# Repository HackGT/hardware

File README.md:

# HackGT Hardware
Custom PCBs, electronics, and embedded hardware solutions

PCBs are designed with EAGLE.

Code can be built and flashed with the Arduino IDE with [ATtiny Core](https://github.com/SpenceKonde/ATTinyCore) installed.
* Be sure to configure the right board, clock speed, etc. in the Tools menu
* With new chips or when changing chip settings, select "Burn Bootloader" to set the correct fuses on the microcontroller (or else uploading code won't work)
	* All of the PCBs listed here do not use a bootloader and must have code uploaded over an ISP programmer
* Upload with Sketch -> Upload Using Programmer (*not* regular Upload -- that's only for Arduinos with a bootloader connected over Serial)
	* To flash manually (saves time when flashing many boards because compilation only happens once), Sketch -> Export compiled Binary. This will export a .hex file that you can then upload with `"C:\Program Files (x86)\Arduino\hardware\tools\avr\bin\avrdude.exe" -c usbasp -p t167 -U flash:w:sketch_name.hex` where `usbasp` is your ISP programmer type and `t167` is the microcontroller specifier.

## Insight

* PCB: `PCBs/checkin-tiny/tiny.brd`
* Code: `Code/Insight` and `Code/Insight_Base` (for Arduino MEGA base station)
* Microcontroller: ATtiny167 @ 8 MHz internal clock
* VCC voltage: 3.3V (**Note: this device *requires* a 5V to 3.3V ISP level shifter to be programmed**)
* Features: 915 MHz radio, MFRC522 NFC interface, USB-C rechargeable battery, 20 pin expansion port

Insight is an inexpensive, handheld board designed to be distributed to sponsors at HackGT's events. It contains an NFC reader on one end and a 915 MHz radio on the other. In typical usage, sponsors scan participant badges over NFC, the device relays the decoded participant UUID to the base station (see below), which pops the participant's information (e.g. name, resume, favorite programming languages) up on the sponsor's phone or laptop. See [HackGT Insight](https://github.com/HackGT/insight) for more information. A 915 MHz radio is used instead of Wi-Fi due to reduced cost, reduced microcontroller requirements, and so that it will have available usable bandwidth even with thousands of 2.4 GHz radios (Wi-Fi / Bluetooth) active during a HackGT event.

The base station consists of an Arduino MEGA with an Ethernet Shield and an [Adafruit RFM69HCW radio module](https://www.adafruit.com/product/3070) added.

### Tech details:
* Power is *always* supplied from the 18650 Lithium Ion battery. This means that a battery must be installed for the device to work -- even if the USB-C connection is plugged in.
* The device **does not have reverse polarity protection**. Always double check the orientation of the Li-Ion battery.
* Voltage is stepped down from the battery's 4.2 volts (max) to 3.5 volts (min) to 3.3 volts VCC by a [linear low-dropout regulator](http://www.ti.com/lit/ds/symlink/tps736.pdf). This regulator drops out at 3.5 volts and can supply up to 400 mA of current.
* USB charging occurs at up to 500 mA (limit of charging IC chosen).
* MFRC522 (NFC) and RFM69HCW (radio) are connected to the ATtiny167 over the chip's hardware SPI bus. The SPI chip select lines are pulled high to deselect them when the ATtiny is programmed over ISP.
* A voltage divider with 4.7K ohm and 10K ohm resistors is used to measure the current battery level from the ATtiny's ADC. This read 10-bit value can then be easily converted to a voltage and/or battery percentage. See `Insight` and `Insight_Base` for the code that does this.
* A TTL serial header is exposed on the bottom edge of the PCB for debugging use. This header does not need to be soldered for final production devices.

### 20-pin expansion header
This device supports shields / daughterboard expansions using the 20-pin expansion header.

With board oriented as seen above:
```
[ 2 | 4 | 6 | 8 | 10 | 12 | 14 | 16 | 18 | 20 ]
[ 1 | 3 | 5 | 7 | 9  | 11 | 13 | 15 | 17 | 19 ]
```

Pin | Signal
----|-------
1 | V_USB (5 volts when USB plugged in, can also be used to charge battery)
2 | V3.3 (3.3 volts when switched on)
3 | RF_IRQ (radio to microcontroller interrupt)
4 | GND
5 | RX (TTL receive)
6 | RED (red status LED)
7 | TX (TTL transmit)
8 | GREEN (green status LED)
9 | BAT_REF (raw voltage divided battery reference, 3.3V safe)
10 | SPEAKER (connected to piezo buzzer, use with `tone()`)
11 | AUX0 (reserved for future use)
12 | NFC_RST (MRFC522 reset)
13 | CE0 (radio SPI chip select)
14 | CE1 (NFC SPI chip select)
15 | MISO (SPI / ISP)
16 | V_USB
17 | SCK (SPI / ISP)
18 | MOSI (SPI/ ISP)
19 | RST (ATtiny reset, ISP)
20 | GND

## ISP 5V to 3.3V Level Shifter

* PCB: `PCBs/checkin-tiny/shifter.brd`
* Code: N/A
* Primary IC: ‎SN74LVC245AN logic level shifter
* VCC voltage: 5V input, 3.3V output

Nearly all HackGT hardware must be programmed over ISP, a protocol used by AVR microcontrollers based on the SPI standard. This can be done with $6 USB programmers such as [this one](https://www.amazon.com/HiLetgo-ATMEGA8-Programmer-USBasp-Cable/dp/B00AX4WQ00). However, note that even though this programmer claims to support 3.3V operation, this only applies to the VCC pin; the signal lines will still operate at 5V. This can damage 5V intolerant devices connected to the SPI bus (e.g. the MFRC522 NFC chip and RFM69HCW radio on Insight).

This tiny board connects to the 6-pin ISP header on the top, shifts the VCC and signal lines down to 3.3 volts, and then outputs these signals on the output ISP header on the bottom. Note that the USB programmer must be outputting 5 volts for this shifter to work correctly so be sure to configure it for 5 volt *not* 3.3 volt output.

**Be sure to double check the correct ISP header orientation when soldering the male/female headers on!**

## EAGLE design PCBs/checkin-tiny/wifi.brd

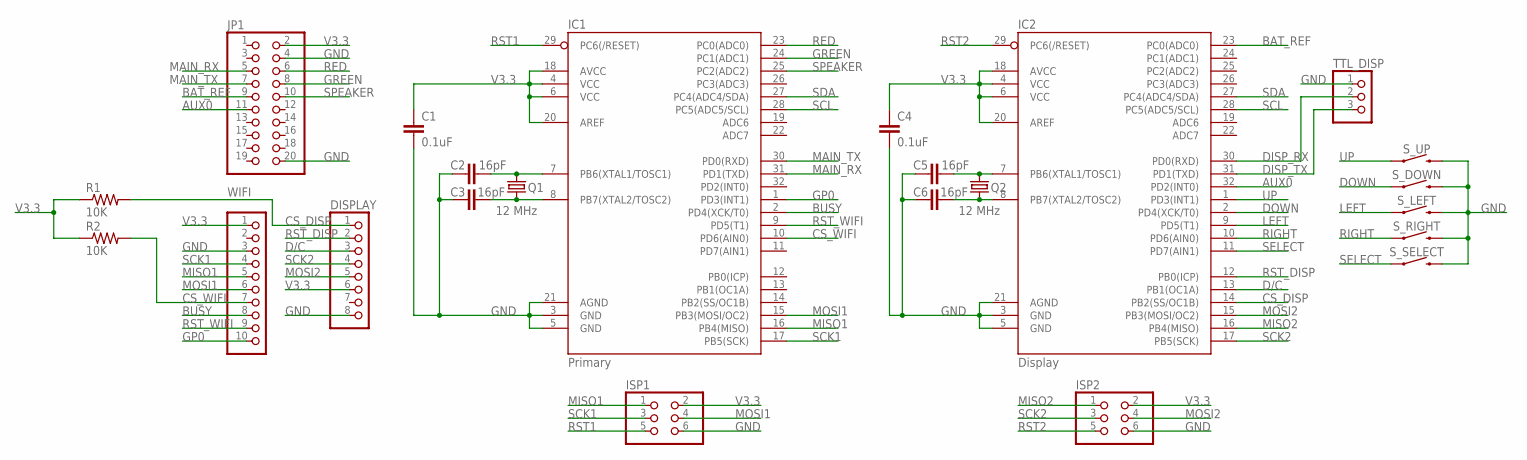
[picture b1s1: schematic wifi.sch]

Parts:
C1, C4: 0.1uF; C1206
C2, C3, C5, C6: 16pF; C1206
DISPLAY: PINHD-1X8CLEANBIG; 1X08-CLEANBIG
IC1: Primary; TQFP32-08
IC2: Display; TQFP32-08
ISP1, ISP2: PINHD-2X3; 2X03
JP1: PINHD-2X10; 2X10
Q1, Q2: 12 MHz; HC49/S
R1, R2: 10K; R1206
S_DOWN: MOMENTARY-SWITCH-SPST-PTH-6.0MM; TACTILE_SWITCH_PTH_6.0MM
S_LEFT: MOMENTARY-SWITCH-SPST-PTH-6.0MM; TACTILE_SWITCH_PTH_6.0MM
S_RIGHT: MOMENTARY-SWITCH-SPST-PTH-6.0MM; TACTILE_SWITCH_PTH_6.0MM
S_SELECT: MOMENTARY-SWITCH-SPST-PTH-6.0MM; TACTILE_SWITCH_PTH_6.0MM
S_UP: MOMENTARY-SWITCH-SPST-PTH-6.0MM; TACTILE_SWITCH_PTH_6.0MM
TTL_DISP: PINHD-1X3; 1X03
WIFI: PINHD-1X10; 1X10-BIG

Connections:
AUX0: IC2.32 (PD2(INT0)), JP1.11
BAT_REF: IC2.23 (PC0(ADC0)), JP1.9
BUSY: IC1.2 (PD4(XCK/T0)), WIFI.8
CS_DISP: DISPLAY.1, IC2.14 (PB2(SS/OC1B)), R1.2
CS_WIFI: IC1.10 (PD6(AIN0)), R2.2, WIFI.7
D/C: DISPLAY.3, IC2.13 (PB1(OC1A))
DISP_RX: IC2.30 (PD0(RXD)), TTL_DISP.2
DISP_TX: IC2.31 (PD1(TXD)), TTL_DISP.3
DOWN: IC2.2 (PD4(XCK/T0)), S_DOWN.1
GND: C1.2, C2.1, C3.1, C4.2, C5.1, C6.1, DISPLAY.8, IC1.3 (GND), IC1.5 (GND), IC1.21 (AGND), IC2.3 (GND), IC2.5 (GND), IC2.21 (AGND), ISP1.6, ISP2.6, JP1.4, JP1.20, S_DOWN.3 (2), S_LEFT.3 (2), S_RIGHT.3 (2), S_SELECT.3 (2), S_UP.3 (2), TTL_DISP.1, WIFI.3
GP0: IC1.1 (PD3(INT1)), WIFI.10
GREEN: IC1.24 (PC1(ADC1)), JP1.8
LEFT: IC2.9 (PD5(T1)), S_LEFT.1
MAIN_RX: IC1.31 (PD1(TXD)), JP1.5
MAIN_TX: IC1.30 (PD0(RXD)), JP1.7
MISO1: IC1.16 (PB4(MISO)), ISP1.1, WIFI.5
MISO2: IC2.16 (PB4(MISO)), ISP2.1
MOSI1: IC1.15 (PB3(MOSI/OC2)), ISP1.4, WIFI.6
MOSI2: DISPLAY.5, IC2.15 (PB3(MOSI/OC2)), ISP2.4
unnamed: C5.2, IC2.7 (PB6(XTAL1/TOSC1)), Q2.2
unnamed: C6.2, IC2.8 (PB7(XTAL2/TOSC2)), Q2.1
unnamed: C2.2, IC1.7 (PB6(XTAL1/TOSC1)), Q1.2
unnamed: C3.2, IC1.8 (PB7(XTAL2/TOSC2)), Q1.1
RED: IC1.23 (PC0(ADC0)), JP1.6
RIGHT: IC2.10 (PD6(AIN0)), S_RIGHT.1
RST1: IC1.29 (PC6(/RESET)), ISP1.5
RST2: IC2.29 (PC6(/RESET)), ISP2.5
RST_DISP: DISPLAY.2, IC2.12 (PB0(ICP))
RST_WIFI: IC1.9 (PD5(T1)), WIFI.9
SCK1: IC1.17 (PB5(SCK)), ISP1.3, WIFI.4
SCK2: DISPLAY.4, IC2.17 (PB5(SCK)), ISP2.3
SCL: IC1.28 (PC5(ADC5/SCL)), IC2.28 (PC5(ADC5/SCL))
SDA: IC1.27 (PC4(ADC4/SDA)), IC2.27 (PC4(ADC4/SDA))
SELECT: IC2.11 (PD7(AIN1)), S_SELECT.1
SPEAKER: IC1.25 (PC2(ADC2)), JP1.10
UP: IC2.1 (PD3(INT1)), S_UP.1
V3.3: C1.1, C4.1, DISPLAY.6, IC1.4 (VCC), IC1.6 (VCC), IC1.18 (AVCC), IC1.20 (AREF), IC2.4 (VCC), IC2.6 (VCC), IC2.18 (AVCC), IC2.20 (AREF), ISP1.2, ISP2.2, JP1.2, R1.1, R2.1, WIFI.1

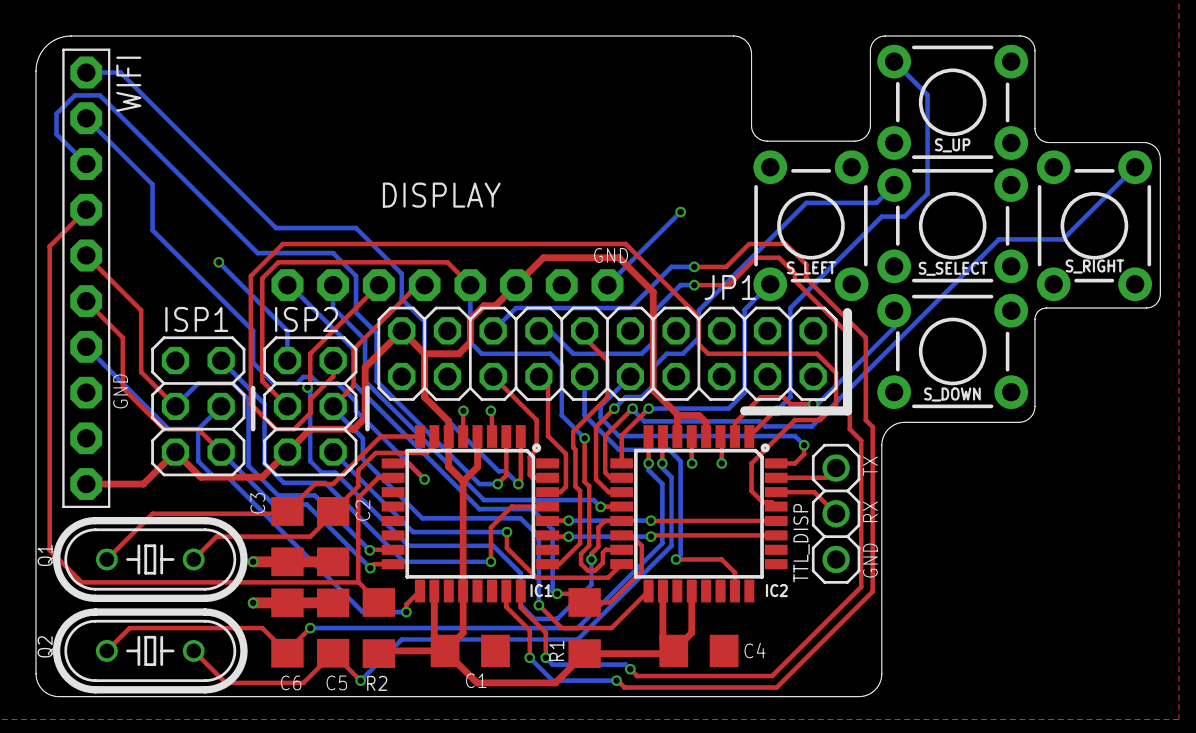
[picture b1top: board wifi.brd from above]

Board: 2 copper layers, 62.5 x 36.7 mm, 23 parts (0 on the bottom side), 37 nets.

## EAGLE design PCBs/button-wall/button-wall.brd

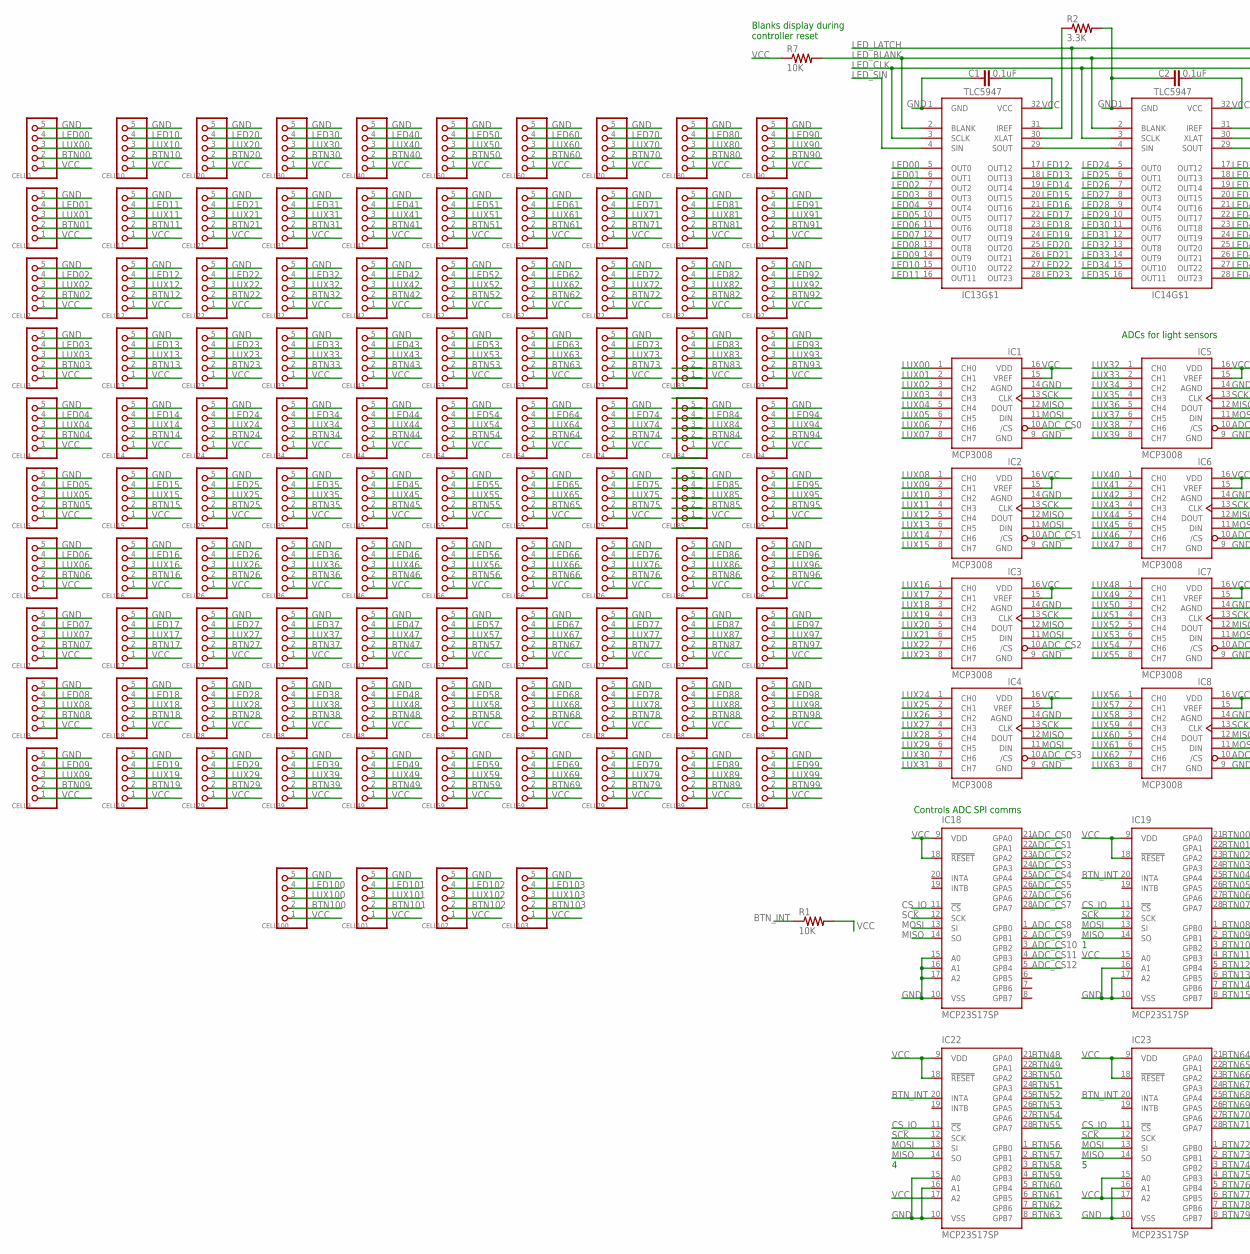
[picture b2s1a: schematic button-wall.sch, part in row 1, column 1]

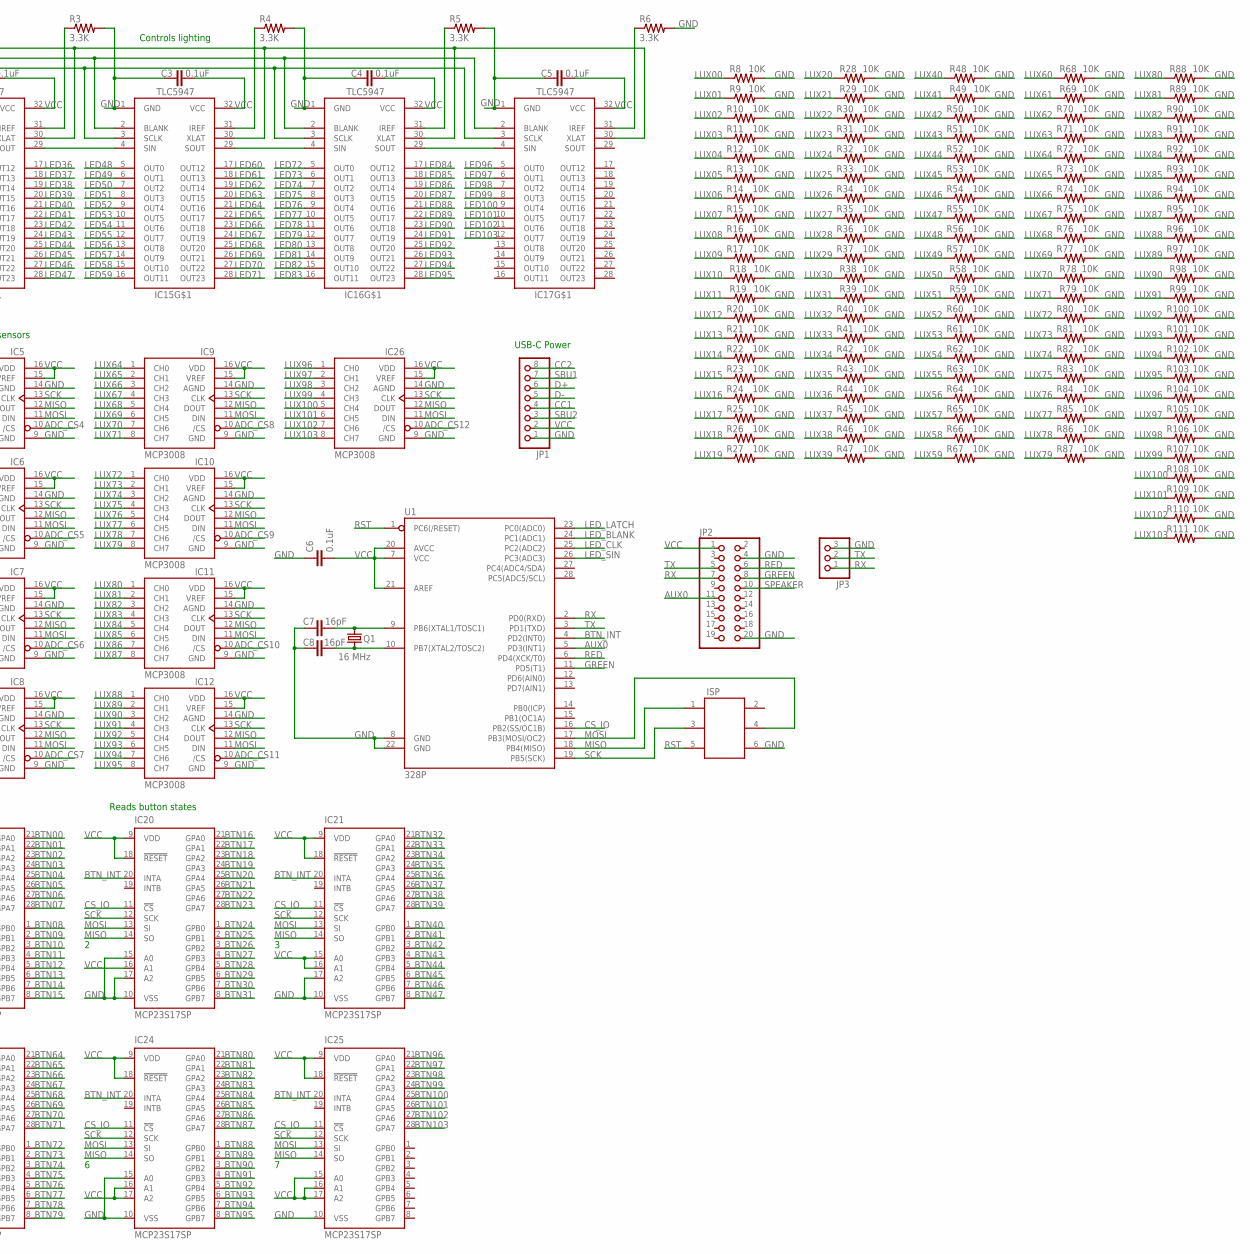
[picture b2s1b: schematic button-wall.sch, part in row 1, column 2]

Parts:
C1, C2, C3, C4, C5, C6: 0.1uF; C1206
C7, C8: 16pF; C0805
CELL0, CELL1, CELL2, CELL3, CELL4, CELL5, CELL6, CELL7, CELL8, CELL9, CELL10, CELL11, CELL12, CELL13, CELL14, CELL15, CELL16, CELL17, CELL18, CELL19, CELL20, CELL21, CELL22, CELL23, CELL24, CELL25, CELL26, CELL27, CELL28, CELL29, CELL30, CELL31, CELL32, CELL33, CELL34, CELL35, CELL36, CELL37, CELL38, CELL39, CELL40, CELL41, CELL42, CELL43, CELL44, CELL45, CELL46, CELL47, CELL48, CELL49, CELL50, CELL51, CELL52, CELL53, CELL54, CELL55, CELL56, CELL57, CELL58, CELL59, CELL60, CELL61, CELL62, CELL63, CELL64, CELL65, CELL66, CELL67, CELL68, CELL69, CELL70, CELL71, CELL72, CELL73, CELL74, CELL75, CELL76, CELL77, CELL78, CELL79, CELL80, CELL81, CELL82, CELL83, CELL84, CELL85, CELL86, CELL87, CELL88, CELL89, CELL90, CELL91, CELL92, CELL93, CELL94, CELL95, CELL96, CELL97, CELL98, CELL99, CELL100, CELL101, CELL102, CELL103: PINHD-1X55X2MM; 1_05X2MM
IC1, IC2, IC3, IC4, IC5, IC6, IC7, IC8, IC9, IC10, IC11, IC12, IC26: MCP3008; DIL16
IC13, IC14, IC15, IC16, IC17: TLC5947-DAP; HTSSOP32DAP
IC18, IC19, IC20, IC21, IC22, IC23, IC24, IC25: MCP23S17SP; DIL28-3
ISP: 61200621621
JP1: PINHD-1X8CLEANBIG; 1X08-CLEANBIG
JP2: PINHD-2X10; 2X10
JP3: PINHD-1X3; 1X03
Q1: 16 MHz; HC49/S
R1, R7: 10K; R1206
R2, R3, R4, R5, R6: 3.3K; R1206
R8, R9, R10, R11, R12, R13, R14, R15, R16, R17, R18, R19, R20, R21, R22, R23, R24, R25, R26, R27, R28, R29, R30, R31, R32, R33, R34, R35, R36, R37, R38, R39, R40, R41, R42, R43, R44, R45, R46, R47, R48, R49, R50, R51, R52, R53, R54, R55, R56, R57, R58, R59, R60, R61, R62, R63, R64, R65, R66, R67, R68, R69, R70, R71, R72, R73, R74, R75, R76, R77, R78, R79, R80, R81, R82, R83, R84, R85, R86, R87, R88, R89, R90, R91, R92, R93, R94, R95, R96, R97, R98, R99, R100, R101, R102, R103, R104, R105, R106, R107, R108, R109, R110, R111: 10K; R0805
U1: 328P; DIP28

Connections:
ADC_CS0: IC1.10 (/CS), IC18.21 (GPA0)
ADC_CS1: IC2.10 (/CS), IC18.22 (GPA1)
ADC_CS2: IC3.10 (/CS), IC18.23 (GPA2)
ADC_CS3: IC4.10 (/CS), IC18.24 (GPA3)
ADC_CS4: IC5.10 (/CS), IC18.25 (GPA4)
ADC_CS5: IC6.10 (/CS), IC18.26 (GPA5)
ADC_CS6: IC7.10 (/CS), IC18.27 (GPA6)
ADC_CS7: IC8.10 (/CS), IC18.28 (GPA7)
ADC_CS8: IC9.10 (/CS), IC18.1 (GPB0)
ADC_CS9: IC10.10 (/CS), IC18.2 (GPB1)
ADC_CS10: IC11.10 (/CS), IC18.3 (GPB2)
ADC_CS11: IC12.10 (/CS), IC18.4 (GPB3)
ADC_CS12: IC18.5 (GPB4), IC26.10 (/CS)
AUX0: JP2.11, U1.5 (PD3(INT1))
BTN00: CELL0.2, IC19.21 (GPA0)
BTN01: CELL1.2, IC19.22 (GPA1)
BTN02: CELL2.2, IC19.23 (GPA2)
BTN03: CELL3.2, IC19.24 (GPA3)
BTN04: CELL4.2, IC19.25 (GPA4)
BTN05: CELL5.2, IC19.26 (GPA5)
BTN06: CELL6.2, IC19.27 (GPA6)
BTN07: CELL7.2, IC19.28 (GPA7)
BTN08: CELL8.2, IC19.1 (GPB0)
BTN09: CELL9.2, IC19.2 (GPB1)
BTN10: CELL10.2, IC19.3 (GPB2)
BTN11: CELL11.2, IC19.4 (GPB3)
BTN12: CELL12.2, IC19.5 (GPB4)
BTN13: CELL13.2, IC19.6 (GPB5)
BTN14: CELL14.2, IC19.7 (GPB6)
BTN15: CELL15.2, IC19.8 (GPB7)
BTN16: CELL16.2, IC20.21 (GPA0)
BTN17: CELL17.2, IC20.22 (GPA1)
BTN18: CELL18.2, IC20.23 (GPA2)
BTN19: CELL19.2, IC20.24 (GPA3)
BTN20: CELL20.2, IC20.25 (GPA4)
BTN21: CELL21.2, IC20.26 (GPA5)
BTN22: CELL22.2, IC20.27 (GPA6)
BTN23: CELL23.2, IC20.28 (GPA7)
BTN24: CELL24.2, IC20.1 (GPB0)
BTN25: CELL25.2, IC20.2 (GPB1)
BTN26: CELL26.2, IC20.3 (GPB2)
BTN27: CELL27.2, IC20.4 (GPB3)
BTN28: CELL28.2, IC20.5 (GPB4)
BTN29: CELL29.2, IC20.6 (GPB5)
BTN30: CELL30.2, IC20.7 (GPB6)
BTN31: CELL31.2, IC20.8 (GPB7)
BTN32: CELL32.2, IC21.21 (GPA0)
BTN33: CELL33.2, IC21.22 (GPA1)
BTN34: CELL34.2, IC21.23 (GPA2)
BTN35: CELL35.2, IC21.24 (GPA3)
BTN36: CELL36.2, IC21.25 (GPA4)
BTN37: CELL37.2, IC21.26 (GPA5)
BTN38: CELL38.2, IC21.27 (GPA6)
BTN39: CELL39.2, IC21.28 (GPA7)
BTN40: CELL40.2, IC21.1 (GPB0)
BTN41: CELL41.2, IC21.2 (GPB1)
BTN42: CELL42.2, IC21.3 (GPB2)
BTN43: CELL43.2, IC21.4 (GPB3)
BTN44: CELL44.2, IC21.5 (GPB4)
BTN45: CELL45.2, IC21.6 (GPB5)
BTN46: CELL46.2, IC21.7 (GPB6)
BTN47: CELL47.2, IC21.8 (GPB7)
BTN48: CELL48.2, IC22.21 (GPA0)
BTN49: CELL49.2, IC22.22 (GPA1)
BTN50: CELL50.2, IC22.23 (GPA2)
BTN51: CELL51.2, IC22.24 (GPA3)
BTN52: CELL52.2, IC22.25 (GPA4)
BTN53: CELL53.2, IC22.26 (GPA5)
BTN54: CELL54.2, IC22.27 (GPA6)
BTN55: CELL55.2, IC22.28 (GPA7)
BTN56: CELL56.2, IC22.1 (GPB0)
BTN57: CELL57.2, IC22.2 (GPB1)
BTN58: CELL58.2, IC22.3 (GPB2)
BTN59: CELL59.2, IC22.4 (GPB3)
BTN60: CELL60.2, IC22.5 (GPB4)
BTN61: CELL61.2, IC22.6 (GPB5)
BTN62: CELL62.2, IC22.7 (GPB6)
BTN63: CELL63.2, IC22.8 (GPB7)
BTN64: CELL64.2, IC23.21 (GPA0)
BTN65: CELL65.2, IC23.22 (GPA1)
BTN66: CELL66.2, IC23.23 (GPA2)
BTN67: CELL67.2, IC23.24 (GPA3)
BTN68: CELL68.2, IC23.25 (GPA4)
BTN69: CELL69.2, IC23.26 (GPA5)
BTN70: CELL70.2, IC23.27 (GPA6)
BTN71: CELL71.2, IC23.28 (GPA7)
BTN72: CELL72.2, IC23.1 (GPB0)
BTN73: CELL73.2, IC23.2 (GPB1)
BTN74: CELL74.2, IC23.3 (GPB2)
BTN75: CELL75.2, IC23.4 (GPB3)
BTN76: CELL76.2, IC23.5 (GPB4)
BTN77: CELL77.2, IC23.6 (GPB5)
BTN78: CELL78.2, IC23.7 (GPB6)
BTN79: CELL79.2, IC23.8 (GPB7)
BTN80: CELL80.2, IC24.21 (GPA0)
BTN81: CELL81.2, IC24.22 (GPA1)
BTN82: CELL82.2, IC24.23 (GPA2)
BTN83: CELL83.2, IC24.24 (GPA3)
BTN84: CELL84.2, IC24.25 (GPA4)
BTN85: CELL85.2, IC24.26 (GPA5)
BTN86: CELL86.2, IC24.27 (GPA6)
BTN87: CELL87.2, IC24.28 (GPA7)
BTN88: CELL88.2, IC24.1 (GPB0)
BTN89: CELL89.2, IC24.2 (GPB1)
BTN90: CELL90.2, IC24.3 (GPB2)
BTN91: CELL91.2, IC24.4 (GPB3)
BTN92: CELL92.2, IC24.5 (GPB4)
BTN93: CELL93.2, IC24.6 (GPB5)
BTN94: CELL94.2, IC24.7 (GPB6)
BTN95: CELL95.2, IC24.8 (GPB7)
BTN96: CELL96.2, IC25.21 (GPA0)
BTN97: CELL97.2, IC25.22 (GPA1)
BTN98: CELL98.2, IC25.23 (GPA2)
BTN99: CELL99.2, IC25.24 (GPA3)
BTN100: CELL100.2, IC25.25 (GPA4)
BTN101: CELL101.2, IC25.26 (GPA5)
BTN102: CELL102.2, IC25.27 (GPA6)
BTN103: CELL103.2, IC25.28 (GPA7)
BTN_INT: IC19.20 (INTA), IC20.20 (INTA), IC21.20 (INTA), IC22.20 (INTA), IC23.20 (INTA), IC24.20 (INTA), IC25.20 (INTA), R1.1, U1.4 (PD2(INT0))
CC1: JP1.4
CC2: JP1.8
CS_IO: IC18.11 (!CS), IC19.11 (!CS), IC20.11 (!CS), IC21.11 (!CS), IC22.11 (!CS), IC23.11 (!CS), IC24.11 (!CS), IC25.11 (!CS), U1.16 (PB2(SS/OC1B))
D+: JP1.6
D-: JP1.5
GND: C1.1, C2.1, C3.1, C4.1, C5.1, C6.1, C7.1, C8.1, CELL0.5, CELL1.5, CELL2.5, CELL3.5, CELL4.5, CELL5.5, CELL6.5, CELL7.5, CELL8.5, CELL9.5, CELL10.5, CELL11.5, CELL12.5, CELL13.5, CELL14.5, CELL15.5, CELL16.5, CELL17.5, CELL18.5, CELL19.5, CELL20.5, CELL21.5, CELL22.5, CELL23.5, CELL24.5, CELL25.5, CELL26.5, CELL27.5, CELL28.5, CELL29.5, CELL30.5, CELL31.5, CELL32.5, CELL33.5, CELL34.5, CELL35.5, CELL36.5, CELL37.5, CELL38.5, CELL39.5, CELL40.5, CELL41.5, CELL42.5, CELL43.5, CELL44.5, CELL45.5, CELL46.5, CELL47.5, CELL48.5, CELL49.5, CELL50.5, CELL51.5, CELL52.5, CELL53.5, CELL54.5, CELL55.5, CELL56.5, CELL57.5, CELL58.5, CELL59.5, CELL60.5, CELL61.5, CELL62.5, CELL63.5, CELL64.5, CELL65.5, CELL66.5, CELL67.5, CELL68.5, CELL69.5, CELL70.5, CELL71.5, CELL72.5, CELL73.5, CELL74.5, CELL75.5, CELL76.5, CELL77.5, CELL78.5, CELL79.5, CELL80.5, CELL81.5, CELL82.5, CELL83.5, CELL84.5, CELL85.5, CELL86.5, CELL87.5, CELL88.5, CELL89.5, CELL90.5, CELL91.5, CELL92.5, CELL93.5, CELL94.5, CELL95.5, CELL96.5, CELL97.5, CELL98.5, CELL99.5, CELL100.5, CELL101.5, CELL102.5, CELL103.5, IC1.9 (GND), IC1.14 (AGND), IC2.9 (GND), IC2.14 (AGND), IC3.9 (GND), IC3.14 (AGND), IC4.9 (GND), IC4.14 (AGND), IC5.9 (GND), IC5.14 (AGND), IC6.9 (GND), IC6.14 (AGND), IC7.9 (GND), IC7.14 (AGND), IC8.9 (GND), IC8.14 (AGND), IC9.9 (GND), IC9.14 (AGND), IC10.9 (GND), IC10.14 (AGND), IC11.9 (GND), IC11.14 (AGND), IC12.9 (GND), IC12.14 (AGND), IC13.1 (GND), IC14.1 (GND), IC15.1 (GND), IC16.1 (GND), IC17.1 (GND), IC18.10 (VSS), IC18.15 (A0), IC18.16 (A1), IC18.17 (A2), IC19.10 (VSS), IC19.16 (A1), IC19.17 (A2), IC20.10 (VSS), IC20.15 (A0), IC20.17 (A2), IC21.10 (VSS), IC21.17 (A2), IC22.10 (VSS), IC22.15 (A0), IC22.16 (A1), IC23.10 (VSS), IC23.16 (A1), IC24.10 (VSS), IC24.15 (A0), IC25.10 (VSS), IC26.9 (GND), IC26.14 (AGND), ISP.6, JP1.1, JP2.4, JP2.20, JP3.3, R2.2, R3.2, R4.2, R5.2, R6.2, R8.2, R9.2, R10.2, R11.2, R12.2, R13.2, R14.2, R15.2, R16.2, R17.2, R18.2, R19.2, R20.2, R21.2, R22.2, R23.2, R24.2, R25.2, R26.2, R27.2, R28.2, R29.2, R30.2, R31.2, R32.2, R33.2, R34.2, R35.2, R36.2, R37.2, R38.2, R39.2, R40.2, R41.2, R42.2, R43.2, R44.2, R45.2, R46.2, R47.2, R48.2, R49.2, R50.2, R51.2, R52.2, R53.2, R54.2, R55.2, R56.2, R57.2, R58.2, R59.2, R60.2, R61.2, R62.2, R63.2, R64.2, R65.2, R66.2, R67.2, R68.2, R69.2, R70.2, R71.2, R72.2, R73.2, R74.2, R75.2, R76.2, R77.2, R78.2, R79.2, R80.2, R81.2, R82.2, R83.2, R84.2, R85.2, R86.2, R87.2, R88.2, R89.2, R90.2, R91.2, R92.2, R93.2, R94.2, R95.2, R96.2, R97.2, R98.2, R99.2, R100.2, R101.2, R102.2, R103.2, R104.2, R105.2, R106.2, R107.2, R108.2, R109.2, R110.2, R111.2, U1.8 (GND), U1.22 (GND)
GREEN: JP2.8, U1.11 (PD5(T1))
LED00: CELL0.4, IC13.5 (OUT0)
LED01: CELL1.4, IC13.6 (OUT1)
LED02: CELL2.4, IC13.7 (OUT2)
LED03: CELL3.4, IC13.8 (OUT3)
LED04: CELL4.4, IC13.9 (OUT4)
LED05: CELL5.4, IC13.10 (OUT5)
LED06: CELL6.4, IC13.11 (OUT6)
LED07: CELL7.4, IC13.12 (OUT7)
LED08: CELL8.4, IC13.13 (OUT8)
LED09: CELL9.4, IC13.14 (OUT9)
LED10: CELL10.4, IC13.15 (OUT10)
LED11: CELL11.4, IC13.16 (OUT11)
LED12: CELL12.4, IC13.17 (OUT12)
LED13: CELL13.4, IC13.18 (OUT13)
LED14: CELL14.4, IC13.19 (OUT14)
LED15: CELL15.4, IC13.20 (OUT15)
LED16: CELL16.4, IC13.21 (OUT16)
LED17: CELL17.4, IC13.22 (OUT17)
LED18: CELL18.4, IC13.23 (OUT18)
LED19: CELL19.4, IC13.24 (OUT19)
LED20: CELL20.4, IC13.25 (OUT20)
LED21: CELL21.4, IC13.26 (OUT21)
LED22: CELL22.4, IC13.27 (OUT22)
LED23: CELL23.4, IC13.28 (OUT23)
LED24: CELL24.4, IC14.5 (OUT0)
LED25: CELL25.4, IC14.6 (OUT1)
LED26: CELL26.4, IC14.7 (OUT2)
LED27: CELL27.4, IC14.8 (OUT3)
LED28: CELL28.4, IC14.9 (OUT4)
LED29: CELL29.4, IC14.10 (OUT5)
LED30: CELL30.4, IC14.11 (OUT6)
LED31: CELL31.4, IC14.12 (OUT7)
LED32: CELL32.4, IC14.13 (OUT8)
LED33: CELL33.4, IC14.14 (OUT9)
LED34: CELL34.4, IC14.15 (OUT10)
LED35: CELL35.4, IC14.16 (OUT11)
LED36: CELL36.4, IC14.17 (OUT12)
LED37: CELL37.4, IC14.18 (OUT13)
LED38: CELL38.4, IC14.19 (OUT14)
LED39: CELL39.4, IC14.20 (OUT15)
LED40: CELL40.4, IC14.21 (OUT16)
LED41: CELL41.4, IC14.22 (OUT17)
LED42: CELL42.4, IC14.23 (OUT18)
LED43: CELL43.4, IC14.24 (OUT19)
LED44: CELL44.4, IC14.25 (OUT20)
LED45: CELL45.4, IC14.26 (OUT21)
LED46: CELL46.4, IC14.27 (OUT22)
LED47: CELL47.4, IC14.28 (OUT23)
LED48: CELL48.4, IC15.5 (OUT0)
LED49: CELL49.4, IC15.6 (OUT1)
LED50: CELL50.4, IC15.7 (OUT2)
LED51: CELL51.4, IC15.8 (OUT3)
LED52: CELL52.4, IC15.9 (OUT4)
LED53: CELL53.4, IC15.10 (OUT5)
LED54: CELL54.4, IC15.11 (OUT6)
LED55: CELL55.4, IC15.12 (OUT7)
LED56: CELL56.4, IC15.13 (OUT8)
LED57: CELL57.4, IC15.14 (OUT9)
LED58: CELL58.4, IC15.15 (OUT10)
LED59: CELL59.4, IC15.16 (OUT11)
LED60: CELL60.4, IC15.17 (OUT12)
LED61: CELL61.4, IC15.18 (OUT13)
LED62: CELL62.4, IC15.19 (OUT14)
LED63: CELL63.4, IC15.20 (OUT15)
LED64: CELL64.4, IC15.21 (OUT16)
LED65: CELL65.4, IC15.22 (OUT17)
LED66: CELL66.4, IC15.23 (OUT18)
LED67: CELL67.4, IC15.24 (OUT19)
LED68: CELL68.4, IC15.25 (OUT20)
LED69: CELL69.4, IC15.26 (OUT21)
LED70: CELL70.4, IC15.27 (OUT22)
LED71: CELL71.4, IC15.28 (OUT23)
LED72: CELL72.4, IC16.5 (OUT0)
LED73: CELL73.4, IC16.6 (OUT1)
LED74: CELL74.4, IC16.7 (OUT2)
LED75: CELL75.4, IC16.8 (OUT3)
LED76: CELL76.4, IC16.9 (OUT4)
LED77: CELL77.4, IC16.10 (OUT5)
LED78: CELL78.4, IC16.11 (OUT6)
LED79: CELL79.4, IC16.12 (OUT7)
LED80: CELL80.4, IC16.13 (OUT8)
LED81: CELL81.4, IC16.14 (OUT9)
LED82: CELL82.4, IC16.15 (OUT10)
LED83: CELL83.4, IC16.16 (OUT11)
LED84: CELL84.4, IC16.17 (OUT12)
LED85: CELL85.4, IC16.18 (OUT13)
LED86: CELL86.4, IC16.19 (OUT14)
LED87: CELL87.4, IC16.20 (OUT15)
LED88: CELL88.4, IC16.21 (OUT16)
LED89: CELL89.4, IC16.22 (OUT17)
LED90: CELL90.4, IC16.23 (OUT18)
LED91: CELL91.4, IC16.24 (OUT19)
LED92: CELL92.4, IC16.25 (OUT20)
LED93: CELL93.4, IC16.26 (OUT21)
LED94: CELL94.4, IC16.27 (OUT22)
LED95: CELL95.4, IC16.28 (OUT23)
LED96: CELL96.4, IC17.5 (OUT0)
LED97: CELL97.4, IC17.6 (OUT1)
LED98: CELL98.4, IC17.7 (OUT2)
LED99: CELL99.4, IC17.8 (OUT3)
LED100: CELL100.4, IC17.9 (OUT4)
LED101: CELL101.4, IC17.10 (OUT5)
LED102: CELL102.4, IC17.11 (OUT6)
LED103: CELL103.4, IC17.12 (OUT7)
LED_BLANK: IC13.2 (BLANK), IC14.2 (BLANK), IC15.2 (BLANK), IC16.2 (BLANK), IC17.2 (BLANK), R7.2, U1.24 (PC1(ADC1))
LED_CLK: IC13.3 (SCLK), IC14.3 (SCLK), IC15.3 (SCLK), IC16.3 (SCLK), IC17.3 (SCLK), U1.25 (PC2(ADC2))
LED_LATCH: IC13.30 (XLAT), IC14.30 (XLAT), IC15.30 (XLAT), IC16.30 (XLAT), IC17.30 (XLAT), U1.23 (PC0(ADC0))
LED_SIN: IC13.4 (SIN), U1.26 (PC3(ADC3))
LUX00: CELL0.3, IC1.1 (CH0), R8.1
LUX01: CELL1.3, IC1.2 (CH1), R9.1
LUX02: CELL2.3, IC1.3 (CH2), R10.1
LUX03: CELL3.3, IC1.4 (CH3), R11.1
LUX04: CELL4.3, IC1.5 (CH4), R12.1
LUX05: CELL5.3, IC1.6 (CH5), R13.1
LUX06: CELL6.3, IC1.7 (CH6), R14.1
LUX07: CELL7.3, IC1.8 (CH7), R15.1
LUX08: CELL8.3, IC2.1 (CH0), R16.1
LUX09: CELL9.3, IC2.2 (CH1), R17.1
LUX10: CELL10.3, IC2.3 (CH2), R18.1
LUX11: CELL11.3, IC2.4 (CH3), R19.1
LUX12: CELL12.3, IC2.5 (CH4), R20.1
LUX13: CELL13.3, IC2.6 (CH5), R21.1
LUX14: CELL14.3, IC2.7 (CH6), R22.1
LUX15: CELL15.3, IC2.8 (CH7), R23.1
LUX16: CELL16.3, IC3.1 (CH0), R24.1
LUX17: CELL17.3, IC3.2 (CH1), R25.1
LUX18: CELL18.3, IC3.3 (CH2), R26.1
LUX19: CELL19.3, IC3.4 (CH3), R27.1
LUX20: CELL20.3, IC3.5 (CH4), R28.1
LUX21: CELL21.3, IC3.6 (CH5), R29.1
LUX22: CELL22.3, IC3.7 (CH6), R30.1
LUX23: CELL23.3, IC3.8 (CH7), R31.1
LUX24: CELL24.3, IC4.1 (CH0), R32.1
LUX25: CELL25.3, IC4.2 (CH1), R33.1
LUX26: CELL26.3, IC4.3 (CH2), R34.1
LUX27: CELL27.3, IC4.4 (CH3), R35.1
LUX28: CELL28.3, IC4.5 (CH4), R36.1
LUX29: CELL29.3, IC4.6 (CH5), R37.1
LUX30: CELL30.3, IC4.7 (CH6), R38.1
LUX31: CELL31.3, IC4.8 (CH7), R39.1
LUX32: CELL32.3, IC5.1 (CH0), R40.1
LUX33: CELL33.3, IC5.2 (CH1), R41.1
LUX34: CELL34.3, IC5.3 (CH2), R42.1
LUX35: CELL35.3, IC5.4 (CH3), R43.1
LUX36: CELL36.3, IC5.5 (CH4), R44.1
LUX37: CELL37.3, IC5.6 (CH5), R45.1
LUX38: CELL38.3, IC5.7 (CH6), R46.1
LUX39: CELL39.3, IC5.8 (CH7), R47.1
LUX40: CELL40.3, IC6.1 (CH0), R48.1
LUX41: CELL41.3, IC6.2 (CH1), R49.1
LUX42: CELL42.3, IC6.3 (CH2), R50.1
LUX43: CELL43.3, IC6.4 (CH3), R51.1
LUX44: CELL44.3, IC6.5 (CH4), R52.1
LUX45: CELL45.3, IC6.6 (CH5), R53.1
LUX46: CELL46.3, IC6.7 (CH6), R54.1
LUX47: CELL47.3, IC6.8 (CH7), R55.1
LUX48: CELL48.3, IC7.1 (CH0), R56.1
LUX49: CELL49.3, IC7.2 (CH1), R57.1
LUX50: CELL50.3, IC7.3 (CH2), R58.1
LUX51: CELL51.3, IC7.4 (CH3), R59.1
LUX52: CELL52.3, IC7.5 (CH4), R60.1
LUX53: CELL53.3, IC7.6 (CH5), R61.1
LUX54: CELL54.3, IC7.7 (CH6), R62.1
LUX55: CELL55.3, R63.1
LUX55.: IC7.8 (CH7)
LUX56: CELL56.3, IC8.1 (CH0), R64.1
LUX57: CELL57.3, IC8.2 (CH1), R65.1
LUX58: CELL58.3, IC8.3 (CH2), R66.1
LUX59: CELL59.3, IC8.4 (CH3), R67.1
LUX60: CELL60.3, IC8.5 (CH4), R68.1
LUX61: CELL61.3, IC8.6 (CH5), R69.1
LUX62: CELL62.3, IC8.7 (CH6), R70.1
LUX63: CELL63.3, IC8.8 (CH7), R71.1
LUX64: CELL64.3, IC9.1 (CH0), R72.1
LUX65: CELL65.3, IC9.2 (CH1), R73.1
LUX66: CELL66.3, IC9.3 (CH2), R74.1
LUX67: CELL67.3, IC9.4 (CH3), R75.1
LUX68: CELL68.3, IC9.5 (CH4), R76.1
LUX69: CELL69.3, IC9.6 (CH5), R77.1
LUX70: CELL70.3, IC9.7 (CH6), R78.1
LUX71: CELL71.3, IC9.8 (CH7), R79.1
LUX72: CELL72.3, IC10.1 (CH0), R80.1
LUX73: CELL73.3, IC10.2 (CH1), R81.1
LUX74: CELL74.3, IC10.3 (CH2), R82.1
LUX75: CELL75.3, IC10.4 (CH3), R83.1
LUX76: CELL76.3, IC10.5 (CH4), R84.1
LUX77: CELL77.3, IC10.6 (CH5), R85.1
LUX78: CELL78.3, IC10.7 (CH6), R86.1
LUX79: CELL79.3, IC10.8 (CH7), R87.1
LUX80: CELL80.3, IC11.1 (CH0), R88.1
LUX81: CELL81.3, IC11.2 (CH1), R89.1
LUX82: CELL82.3, IC11.3 (CH2), R90.1
LUX83: CELL83.3, IC11.4 (CH3), R91.1
LUX84: CELL84.3, IC11.5 (CH4), R92.1
LUX85: CELL85.3, IC11.6 (CH5), R93.1
LUX86: CELL86.3, IC11.7 (CH6), R94.1
LUX87: CELL87.3, IC11.8 (CH7), R95.1
LUX88: CELL88.3, IC12.1 (CH0), R96.1
LUX89: CELL89.3, IC12.2 (CH1), R97.1
LUX90: CELL90.3, IC12.3 (CH2), R98.1
LUX91: CELL91.3, IC12.4 (CH3), R99.1
LUX92: CELL92.3, IC12.5 (CH4), R100.1
LUX93: CELL93.3, IC12.6 (CH5), R101.1
LUX94: CELL94.3, IC12.7 (CH6), R102.1
LUX95: CELL95.3, IC12.8 (CH7), R103.1
LUX96: CELL96.3, IC26.1 (CH0), R104.1
LUX97: CELL97.3, IC26.2 (CH1), R105.1
LUX98: CELL98.3, IC26.3 (CH2), R106.1
LUX99: CELL99.3, IC26.4 (CH3), R107.1
LUX100: CELL100.3, IC26.5 (CH4), R108.1
LUX101: CELL101.3, IC26.6 (CH5), R109.1
LUX102: CELL102.3, IC26.7 (CH6), R110.1
LUX103: CELL103.3, IC26.8 (CH7), R111.1
MISO: IC1.12 (DOUT), IC2.12 (DOUT), IC3.12 (DOUT), IC4.12 (DOUT), IC5.12 (DOUT), IC6.12 (DOUT), IC7.12 (DOUT), IC8.12 (DOUT), IC9.12 (DOUT), IC10.12 (DOUT), IC11.12 (DOUT), IC12.12 (DOUT), IC18.14 (SO), IC19.14 (SO), IC20.14 (SO), IC21.14 (SO), IC22.14 (SO), IC23.14 (SO), IC24.14 (SO), IC25.14 (SO), IC26.12 (DOUT), ISP.1, U1.18 (PB4(MISO))
MOSI: IC1.11 (DIN), IC2.11 (DIN), IC3.11 (DIN), IC4.11 (DIN), IC5.11 (DIN), IC6.11 (DIN), IC7.11 (DIN), IC8.11 (DIN), IC9.11 (DIN), IC10.11 (DIN), IC11.11 (DIN), IC12.11 (DIN), IC18.13 (SI), IC19.13 (SI), IC20.13 (SI), IC21.13 (SI), IC22.13 (SI), IC23.13 (SI), IC24.13 (SI), IC25.13 (SI), IC26.11 (DIN), ISP.4, U1.17 (PB3(MOSI/OC2))
unnamed: IC13.31 (IREF), R2.1
unnamed: C7.2, Q1.2, U1.9 (PB6(XTAL1/TOSC1))
unnamed: C8.2, Q1.1, U1.10 (PB7(XTAL2/TOSC2))
unnamed: IC13.29 (SOUT), IC14.4 (SIN)
unnamed: IC14.29 (SOUT), IC15.4 (SIN)
unnamed: IC15.29 (SOUT), IC16.4 (SIN)
unnamed: IC16.29 (SOUT), IC17.4 (SIN)
unnamed: IC14.31 (IREF), R3.1
unnamed: IC16.31 (IREF), R5.1
unnamed: IC15.31 (IREF), R4.1
unnamed: IC17.31 (IREF), R6.1
RED: JP2.6, U1.6 (PD4(XCK/T0))
RST: ISP.5, U1.1 (PC6(/RESET))
RX: JP2.7, JP3.1, U1.2 (PD0(RXD))
SBU1: JP1.7
SBU2: JP1.3
SCK: IC1.13 (CLK), IC2.13 (CLK), IC3.13 (CLK), IC4.13 (CLK), IC5.13 (CLK), IC6.13 (CLK), IC7.13 (CLK), IC8.13 (CLK), IC9.13 (CLK), IC10.13 (CLK), IC11.13 (CLK), IC12.13 (CLK), IC18.12 (SCK), IC19.12 (SCK), IC20.12 (SCK), IC21.12 (SCK), IC22.12 (SCK), IC23.12 (SCK), IC24.12 (SCK), IC25.12 (SCK), IC26.13 (CLK), ISP.3, U1.19 (PB5(SCK))
SPEAKER: JP2.10
TX: JP2.5, JP3.2, U1.3 (PD1(TXD))
VCC: C1.2, C2.2, C3.2, C4.2, C5.2, C6.2, CELL0.1, CELL1.1, CELL2.1, CELL3.1, CELL4.1, CELL5.1, CELL6.1, CELL7.1, CELL8.1, CELL9.1, CELL10.1, CELL11.1, CELL12.1, CELL13.1, CELL14.1, CELL15.1, CELL16.1, CELL17.1, CELL18.1, CELL19.1, CELL20.1, CELL21.1, CELL22.1, CELL23.1, CELL24.1, CELL25.1, CELL26.1, CELL27.1, CELL28.1, CELL29.1, CELL30.1, CELL31.1, CELL32.1, CELL33.1, CELL34.1, CELL35.1, CELL36.1, CELL37.1, CELL38.1, CELL39.1, CELL40.1, CELL41.1, CELL42.1, CELL43.1, CELL44.1, CELL45.1, CELL46.1, CELL47.1, CELL48.1, CELL49.1, CELL50.1, CELL51.1, CELL52.1, CELL53.1, CELL54.1, CELL55.1, CELL56.1, CELL57.1, CELL58.1, CELL59.1, CELL60.1, CELL61.1, CELL62.1, CELL63.1, CELL64.1, CELL65.1, CELL66.1, CELL67.1, CELL68.1, CELL69.1, CELL70.1, CELL71.1, CELL72.1, CELL73.1, CELL74.1, CELL75.1, CELL76.1, CELL77.1, CELL78.1, CELL79.1, CELL80.1, CELL81.1, CELL82.1, CELL83.1, CELL84.1, CELL85.1, CELL86.1, CELL87.1, CELL88.1, CELL89.1, CELL90.1, CELL91.1, CELL92.1, CELL93.1, CELL94.1, CELL95.1, CELL96.1, CELL97.1, CELL98.1, CELL99.1, CELL100.1, CELL101.1, CELL102.1, CELL103.1, IC1.15 (VREF), IC1.16 (VDD), IC2.15 (VREF), IC2.16 (VDD), IC3.15 (VREF), IC3.16 (VDD), IC4.15 (VREF), IC4.16 (VDD), IC5.15 (VREF), IC5.16 (VDD), IC6.15 (VREF), IC6.16 (VDD), IC7.15 (VREF), IC7.16 (VDD), IC8.15 (VREF), IC8.16 (VDD), IC9.15 (VREF), IC9.16 (VDD), IC10.15 (VREF), IC10.16 (VDD), IC11.15 (VREF), IC11.16 (VDD), IC12.15 (VREF), IC12.16 (VDD), IC13.32 (VCC), IC14.32 (VCC), IC15.32 (VCC), IC16.32 (VCC), IC17.32 (VCC), IC18.9 (VDD), IC18.18 (!RESET), IC19.9 (VDD), IC19.15 (A0), IC19.18 (!RESET), IC20.9 (VDD), IC20.16 (A1), IC20.18 (!RESET), IC21.9 (VDD), IC21.15 (A0), IC21.16 (A1), IC21.18 (!RESET), IC22.9 (VDD), IC22.17 (A2), IC22.18 (!RESET), IC23.9 (VDD), IC23.15 (A0), IC23.17 (A2), IC23.18 (!RESET), IC24.9 (VDD), IC24.16 (A1), IC24.17 (A2), IC24.18 (!RESET), IC25.9 (VDD), IC25.15 (A0), IC25.16 (A1), IC25.17 (A2), IC25.18 (!RESET), IC26.15 (VREF), IC26.16 (VDD), JP1.2, JP2.1, R1.2, R7.1, U1.7 (VCC), U1.20 (AVCC), U1.21 (AREF)

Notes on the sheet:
Controls ADC SPI comms
ADCs for light sensors
Reads button states
Controls lighting
USB-C Power
Blanks display during controller reset

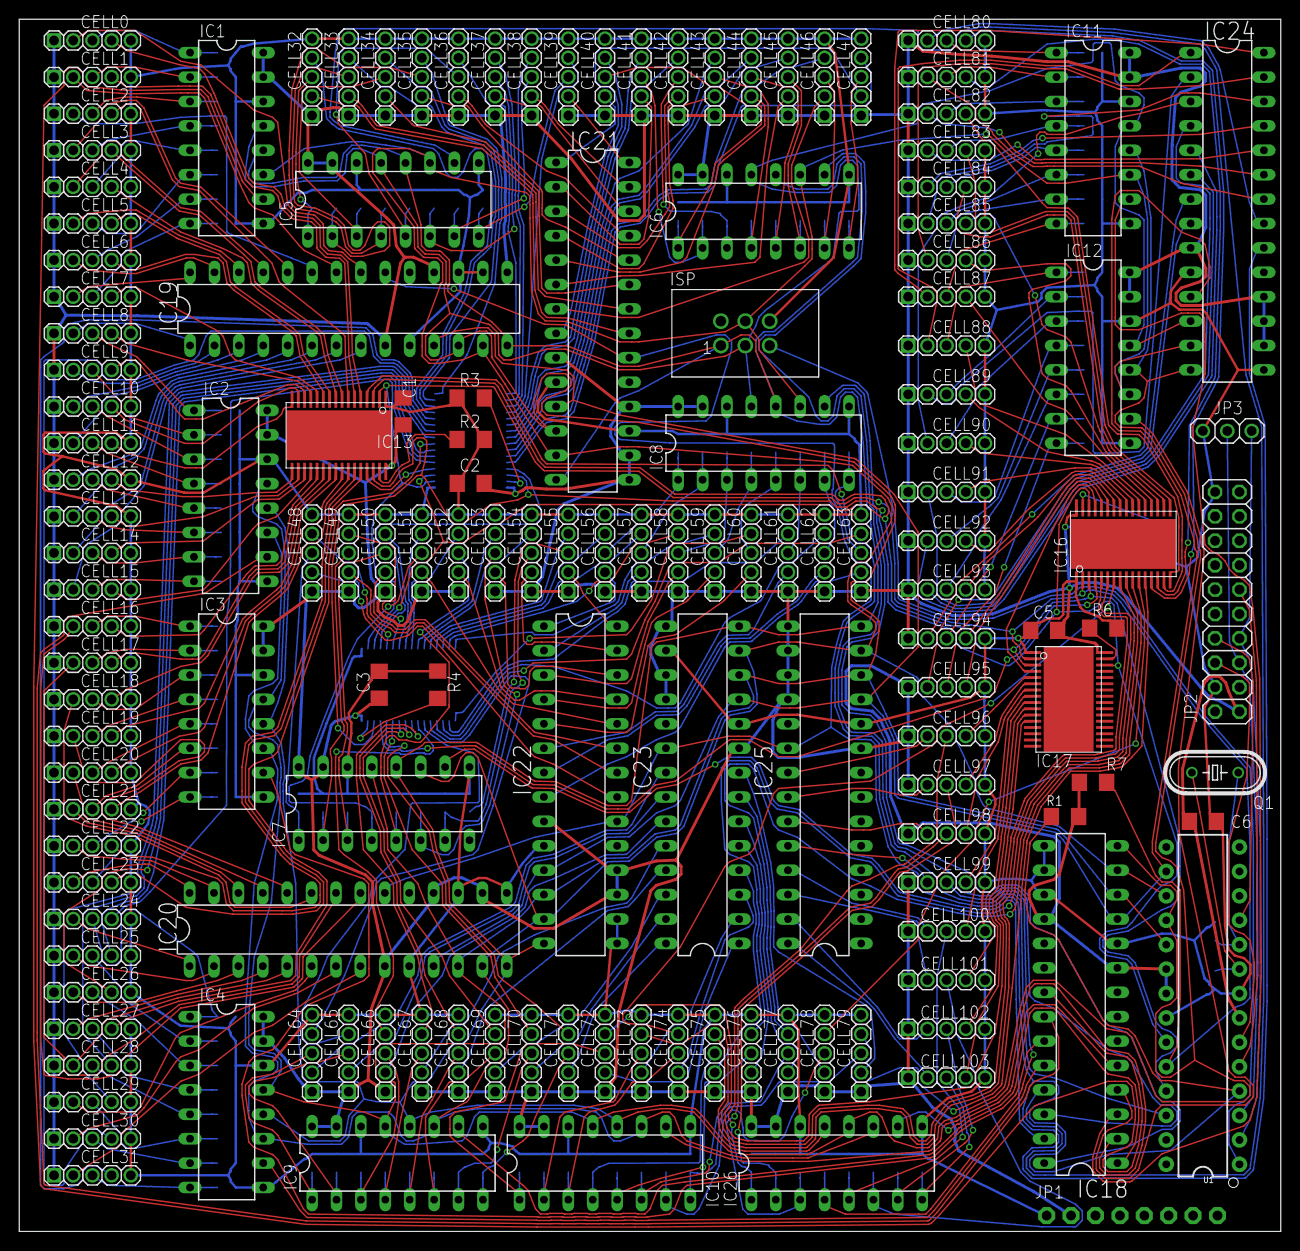
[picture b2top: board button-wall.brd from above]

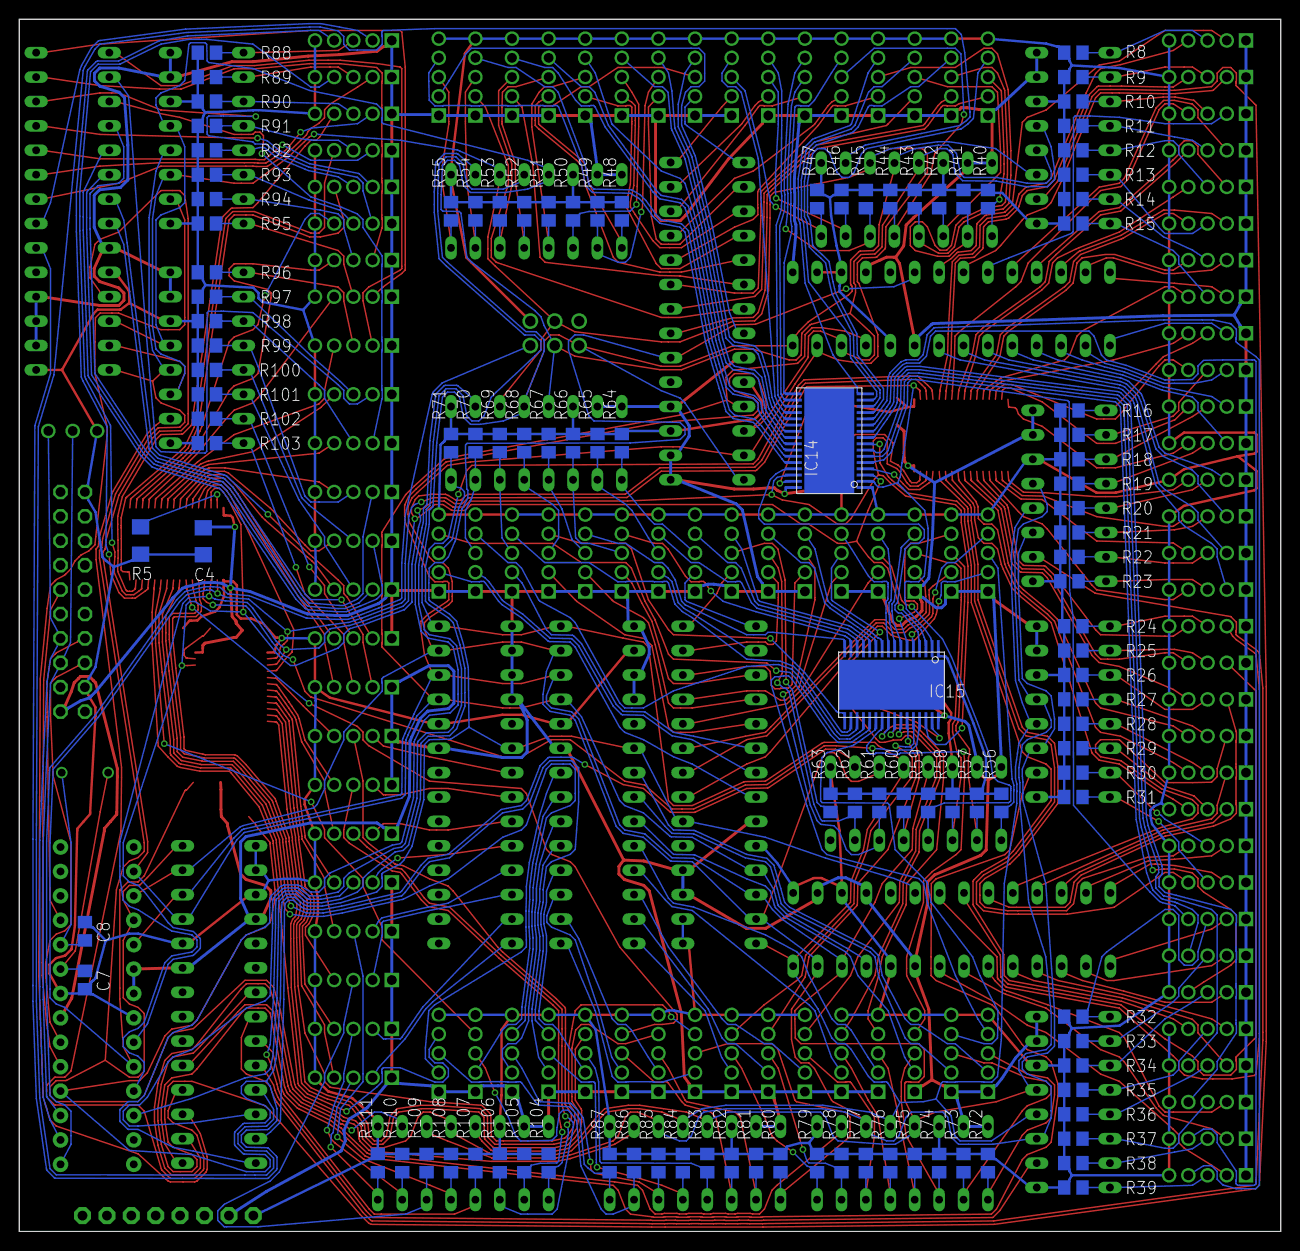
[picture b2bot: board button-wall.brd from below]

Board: 2 copper layers, 131.3 x 126.2 mm, 255 parts (110 on the bottom side), 353 nets.

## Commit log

2020-02-01 Add hardware and corresponding code used for HackGT 6
2020-02-01 Fix incomplete tag check-in code in Insight codebase
2020-02-01 Add DigiKey bill-of-materials (BOMs)
2020-02-01 Add Insight board write-up to README
2020-02-01 Add documentation for 20-pin expansion header
2020-02-01 Add ISP level shifter
2020-02-01 Fix image link
2020-04-19 Fix resistor labels on Wi-Fi board
2020-04-19 Add initial NFC spec

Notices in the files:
parts and their libraries:
Wurth_Elektronik_Electromechanic_Wire_to: Copyright: Würth Elektronik
SparkFun-IC-Microcontroller: Licensing: Creative Commons ShareAlike 4.0 International - https://creativecommons.org/licenses/by-sa/4.0
